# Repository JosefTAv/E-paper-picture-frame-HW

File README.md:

# E-paper-picture-frame-HW
Hardware files for ESP32 based E-paper picture frame

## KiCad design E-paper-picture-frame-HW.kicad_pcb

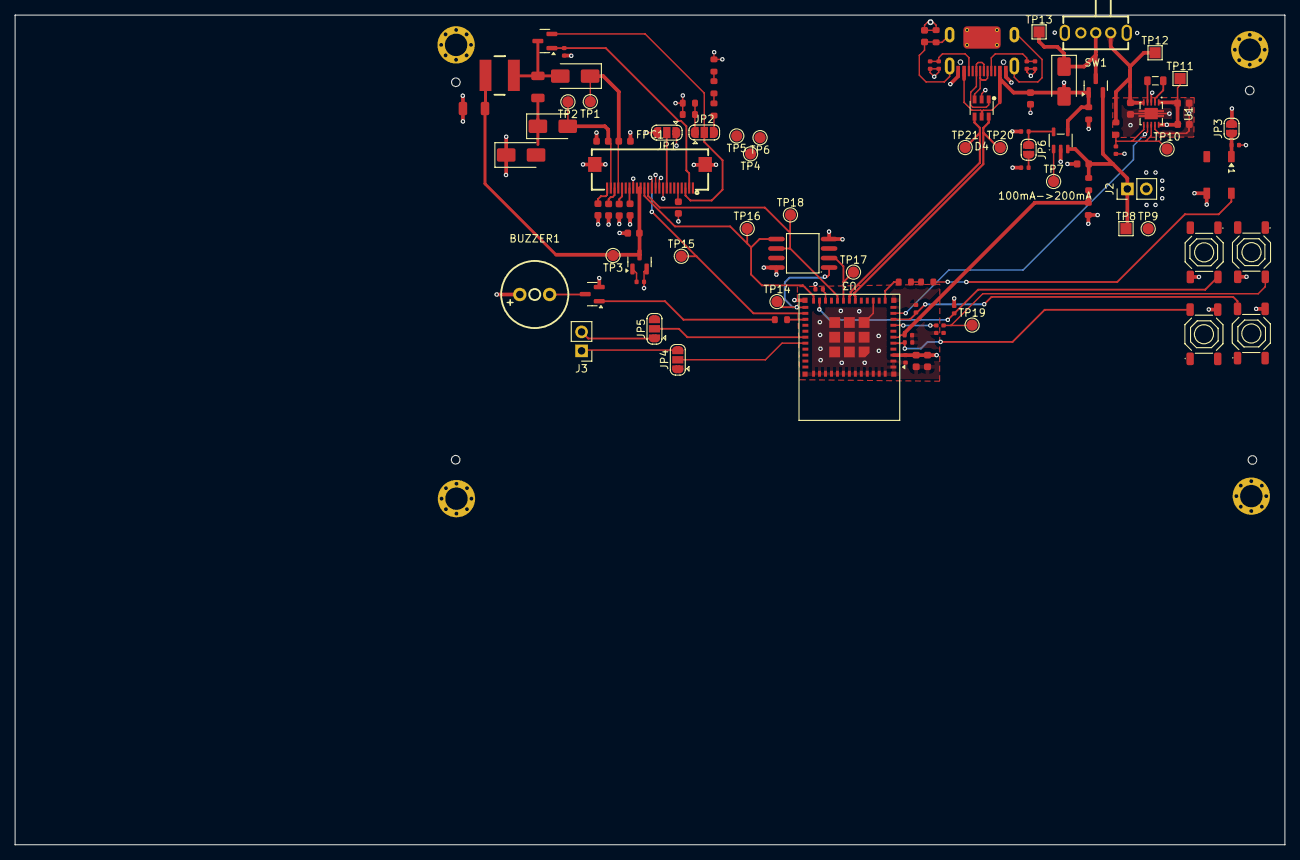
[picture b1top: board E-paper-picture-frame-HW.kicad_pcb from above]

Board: 4 copper layers, 170.2 x 111.2 mm, 110 parts (0 on the bottom side), 63 nets.

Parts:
BUZZER1: YS-MBZ9042C03R16; BUZ-TH_BD9.0-P4.00-D0.6-FD
C1, C3, C4, C5, C6, C8, C9, C10: 1uF; C_0603
C2, C7: 4.7uF; C_1206
C11, C17, C18, C19, C20, C24, C25, C27: 10uF; C_0603
C12, C13, C14, C15, C16, C26: 100nF; C_0402
C23: 1uF; C_0402
D1, D2, D3, D6: SS14; D_SMA
D4: USBLC6-2SC6; SOT-23-6_L2.9-W1.6-P0.95-LS2.8-BL
D5: WS2812B; LED_WS2812B_PLCC4_5.0x5.0mm_P3.2mm
FPC1: AFC24-S24FIA-00; FPC-SMD_P0.50-24P_QCHF-SM-H2.0
H1, H2, H3, H4: Hole, 3mm
H5, H6, H7, H8: Hole_Tooling_JLCPCB
J1: Connector, USB-TYPE-C-16P; TYPE-C-SMD_HX-TYPE-C-16PIN
J2, J3: Conn_01x02; PinHeader_1x02_P2.54mm_Vertical
JP1, JP2, JP4, JP5: SolderJumper_3_Open; SolderJumper-3_P1.3mm_Open_RoundedPad1.0x1.5mm
JP3, JP6: SolderJumper_2_Open; SolderJumper-2_P1.3mm_Open_RoundedPad1.0x1.5mm
L1: SMNR5040-100MT; IND-SMD_2P-L5.0-W5.0
L2: 2.2uH,50mA; L_0805
Q1, Q4: AO3401A; Q_SOT-23
Q2: BSS138; Q_SOT-23
Q3: AO3400A; Q_SOT-23
R1, R2, R11, R12, R13, R14, R19, R24, R25, R26, R27: 10kΩ; R_0402
R3, R4, R5, R6, R7: 1Ω; R_0603
R8, R17, R18, R20: 1MΩ; R_0603
R9, R10, R15, R16: 100Ω; R_0603
S1, S2, S3, S4: Tactile Button, 160gf; SW-SMD_4P-L5.1-W5.1-P3.70-LS6.5-TL-2
SW1: SK12D07VG4; SW-TH_SK12D07VG4
TP1: TestPoint_PREVGH; TestPoint_Pad_D1.5mm
TP2: TestPoint_PREVGL; TestPoint_Pad_D1.5mm
TP3: TestPoint_EPD3V3; TestPoint_Pad_D1.5mm
TP4: TestPoint_CSB; TestPoint_Pad_D1.5mm
TP5: TestPoint_EPD_DC; TestPoint_Pad_D1.5mm
TP6: TestPoint_EPD_RST; TestPoint_Pad_D1.5mm
TP7: TestPoint_CHRG; TestPoint_Pad_D1.5mm
TP8: TestPoint_LIPO; TestPoint_Pad_1.5x1.5mm
TP9: TestPoint_GND; TestPoint_Pad_D1.5mm
TP10: TestPoint_VINA; TestPoint_Pad_D1.5mm
TP11: TestPoint_3V3; TestPoint_Pad_1.5x1.5mm
TP12, TP13: TestPoint_VDD; TestPoint_Pad_1.5x1.5mm
TP14: TestPoint_CS1; TestPoint_Pad_D1.5mm
TP15: TestPoint_CS0; TestPoint_Pad_D1.5mm
TP16: TestPoint_MOSI; TestPoint_Pad_D1.5mm
TP17: TestPoint_MISO; TestPoint_Pad_D1.5mm
TP18: TestPoint_SCK; TestPoint_Pad_D1.5mm
TP19, TP20, TP21: TestPoint_EN; TestPoint_Pad_D1.5mm
U1: TPS63001DRCR; VSON-10_L3.0-W3.0-P0.50-TL-EP_TPS62410DRCR
U2: TP4054; SOT-23-5_L3.0-W1.7-P0.95-LS2.8-BL
U3: ESP32-C6-MINI-1
U4: W25Q128; SOIC-8_L5.3-W5.3-P1.27-LS8.0-BL

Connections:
+3.3V: BUZZER1.1, C19.1, C20.1, C24.1, C25.1, C26.1, JP1.1 (A), Q1.2 (S), R1.1, R24.1, R25.1, R26.1, TP11.1, U1.1 (VOUT), U1.10 (FB), U3.3 (3V3), U4.8 (VCC)
/Display/BS: FPC1.8, JP1.2 (C)
/Display/EPD3V3: C2.1, C3.1, FPC1.15, FPC1.16, L1.1, Q1.3 (D), TP3.1
/Display/EPD3V3_EN: Q1.1 (G), R1.2
/Display/EPD BUSY(CSB): FPC1.9, TP4.1
/Display/EPD CS: FPC1.12, TP15.1, U3.26 (IO20)
/Display/EPD DC: FPC1.11, TP5.1
/Display/EPD RST: FPC1.10, TP6.1
/Display/GDR: FPC1.2, Q2.1 (G), R2.1
/Display/PREVGH: C6.1, D3.1, FPC1.21, TP1.1
/Display/PREVGL: C9.1, D2.2, FPC1.23, TP2.1
/Display/RESE: FPC1.3, JP2.2 (C), Q2.2 (S)
/Display/SPI.MISO: TP17.1, U3.19 (IO14), U4.2 (DO)
/Display/SPI.MOSI: FPC1.14, TP16.1, U3.24 (IO18), U4.5 (DI)
/Display/SPI.SCK: FPC1.13, TP18.1, U3.20 (IO15), U4.6 (CLK)
/IO/5V_USB: C17.1, D4.5, D6.2, J1.A9B4 (VBUS), J1.B9A4 (VBUS), JP3.2 (B), Q4.1 (G), R20.1, U2.4 (VCC)
/IO/BAT+: C27.1, J2.1, Q4.2 (S), R17.1, TP8.1, U2.3 (BAT)
/IO/BUZZER_CTRL: R16.2, U3.27 (IO21)
/IO/CHRG: TP7.1, U2.1 (CHRG)
/IO/CS: TP14.1, U3.25 (IO19), U4.1 (CS#)
/IO/DIN: D5.4 (DIN), R10.2
/IO/EN: C15.1, R15.2, TP10.1, U1.6 (EN), U1.8 (VINA)
/IO/L1: L2.2, U1.4 (L1)
/IO/L2: L2.1, U1.2 (L2)
/IO/LED_DIN: R9.1, U3.12 (IO0)
/IO/LED_VDD: C13.1, D5.1 (VDD), JP3.1 (A)
/IO/PROG: JP6.1 (A), R19.1, U2.5 (PROG)
/IO/PS/SYNC: U1.7 (PS/SYNC), U3.10 (IO5)
/IO/USBCC1: J1.A5 (CC1), R13.1, R14.1
/IO/USBCC2: J1.B5 (CC2), R11.1, R12.1
/IO/USB_Dn: D4.3, J1.A7 (D-), J1.B7 (D-)
/IO/USB_Dp: D4.1, J1.A6 (D+), J1.B6 (D+)
/IO/USB_SHIELD: C11.1, J1.S1 (SHIELD), R8.1
/IO/USER0: C12.1, S1.2 (B), U3.9 (IO4)
/IO/USER1: C14.1, S2.2 (B), U3.5 (IO2)
/IO/VBAT_MON: C16.1, R17.2, R18.1, U3.6 (IO3)
/IO/VDD_EXT: C18.1, R15.1, SW1.1, TP12.1, U1.5 (VIN)
/IO/VDD_EXT_OPEN: D6.1, Q4.3 (D), SW1.2, TP13.1
/MCU/Boot: R25.2, S4.2 (B), U3.23 (IO9)
/MCU/EN: C23.1, R24.2, S3.2 (B), TP19.1, U3.8 (EN)
/MCU/GPIO8: R26.2, U3.22 (IO8)
/MCU/GPIO16: JP5.2 (C), U3.30 (RXD0)
/MCU/GPIO17: JP4.2 (C), U3.31 (TXD0)
/MCU/RX: J3.1, JP4.3 (B)
/MCU/TX: J3.2, JP5.1 (A)
/MCU/USB D+: D4.6, TP20.1, U3.17 (IO12)
/MCU/USB D-: D4.4, TP21.1, U3.18 (IO13)
GNDD: C1.1, C2.2, C3.2, C4.2, C5.2, C6.2, C8.2, C9.2, C10.2, C11.2, C12.2, C13.2, C14.2, C15.2, C16.2, C17.2, C18.2, C19.2, C20.2, C23.2, C24.2, C25.2, C26.2, C27.2, D1.1, D4.2, D5.3 (VSS), FPC1.17, FPC1.25, FPC1.26, H1.1, H2.1, H3.1, H4.1, J1.A12B1 (GND), J1.B12A1 (GND), J2.2, JP1.3 (B), Q3.2 (S), R2.2, R5.2, R6.2, R7.2, R8.2, R11.2, R12.2, R13.2, R14.2, R18.2, R19.2, R20.2, R27.2, S1.4 (D), S2.4 (D), S3.4 (D), S4.4 (D), SW1.4, SW1.5, TP9.1, U1.3 (PGND), U1.9 (GND), U1.11 (PAD), U2.2 (GND), U3.1 (GND), U3.2 (GND), U3.11 (GND), U3.14 (GND), U3.36 (GND), U3.37 (GND), U3.38 (GND), U3.39 (GND), U3.40 (GND), U3.41 (GND), U3.42 (GND), U3.43 (GND), U3.44 (GND), U3.45 (GND), U3.46 (GND), U3.47 (GND), U3.48 (GND), U3.49 (GND), U3.50 (GND), U3.51 (GND), U3.52 (GND), U3.53 (GND), U4.4 (GND)
unnamed: C1.2, FPC1.5
unnamed: C4.1, FPC1.18
unnamed: C5.1, FPC1.20
unnamed: C7.1, D1.2, D2.1
unnamed: C8.1, FPC1.22
unnamed: C10.1, FPC1.24
unnamed: JP2.1 (A), R6.1, R7.1
unnamed: JP2.3 (B), R3.1
unnamed: JP6.2 (B), R27.1
unnamed: C7.2, D3.2, L1.2, Q2.3 (D)
unnamed: BUZZER1.2, Q3.3 (D)
unnamed: Q3.1 (G), R16.1
unnamed: R3.2, R4.1
unnamed: R4.2, R5.1
unnamed: R9.2, R10.1

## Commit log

2026-02-28 Create project
2026-02-28 Initial structure
2026-02-28 First draft of USB and power module Plus some display started
2026-03-03 Only missing Eframe - Mostly finished MCU - Added Test points to IO - Added LiPo charger - Added Power Source Selection - Added SD card module + SPI connections
2026-03-03 Added eframe circuit: - Must replace 10uF caps with higher voltage rated ones - Should double check all the wiring - Assign MCU GPIOs now that all peripherals have their pins assigned
2026-03-17 Final touches on schematic: Added test points Added LED Fixed symbol footprints
2026-03-20 Schematic cleanup and initial layout complete
2026-03-23 Small cleanup + linked jlcpcb parts for ordering
2026-03-29 Changed some parts for more common ones
2026-03-30 Finished USB, SD card and Power Mmt layout
2026-04-05 First draft of layout done. Needs cleaning and DRC
